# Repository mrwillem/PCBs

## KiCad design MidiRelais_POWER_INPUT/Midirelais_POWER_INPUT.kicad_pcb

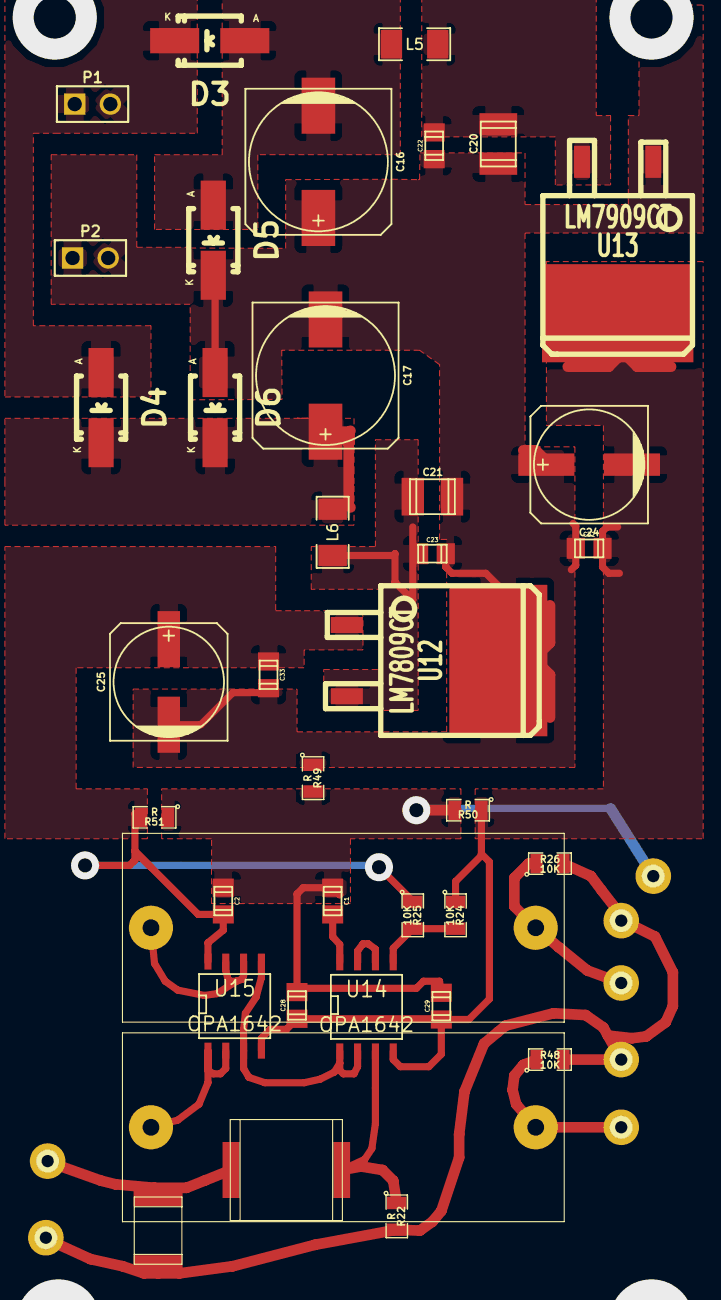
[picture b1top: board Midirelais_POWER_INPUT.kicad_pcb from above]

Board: 2 copper layers, 45 parts (0 on the bottom side), 19 nets.

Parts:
C1, C2, C22, C23, C28, C29, C32, C33: 100nF; c_0805
C16, C17: 470 uF; c_elec_10x10.5
C20, C21: 10uF; c_1210
C24, C25: 47 uF; c_elec_8x6.5
C26: 68pF; Capacitor-Wima-SMD1812-100v-L4,8
C27: 1uF; Capacitor-Wima-SMD2824-63v-L7,2
C30, C31: 10uF; Capacitor-Wima-MKS4-100v-R27K5B13
D3, D4, D5, D6: DIODE; Diode-SMA_Handsoldering_RevA_27July2010
L5, L6: 15 uH 0.08 R; SM1206
P1, P2: CONN_2; PIN_ARRAY_2X1
P3, P12, P13, P14, P15, P16, P17: CONN_1; connect-PAD-01
R22, R49, R50, R51: R; SM0805
R24, R25, R26, R48: 10K; SM0805
U12: LM7809CT; TO263-2
U13: LM7909CT; TO263-2
U14, U15: OPA1642; SO8N

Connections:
AGND: C1.2, C2.2, C28.1, C29.1, P3.1, R49.2, R50.2, R51.1
GND: C26.2, P13.1, P14.1, P15.1, R22.2, R26.2, R48.2
unnamed: C30.2, P16.1, R26.1
unnamed: C31.2, P17.1, R48.1
unnamed: U14.6, U14.7
unnamed: C24.2, C28.2, C29.2, C32.1, R24.1, R50.1, U13.2, U14.4, U15.4
unnamed: C17.1, D4.2, D6.2, L6.1
unnamed: D3.2, D4.1, P1.1, P1.2
unnamed: C16.2, D3.1, D5.1, L5.1
unnamed: C26.1, C27.1, P12.1
unnamed: C27.2, R22.1, U14.3
unnamed: C1.1, C2.1, C25.1, C33.2, R25.1, R51.2, U12.1, U14.8, U15.8
unnamed: R24.2, R25.2, U14.5
unnamed: C20.1, C22.1, L5.2, U13.3
unnamed: C21.2, C23.2, L6.2, U12.3
unnamed: C31.1, U15.1, U15.2
unnamed: C16.1, C17.2, C20.2, C21.1, C22.2, C23.1, C24.1, C25.2, C32.2, C33.1, D5.2, D6.1, P2.1, P2.2, R49.1, U12.2, U13.1
unnamed: U14.1, U14.2, U15.3, U15.5
unnamed: C30.1, U15.6, U15.7

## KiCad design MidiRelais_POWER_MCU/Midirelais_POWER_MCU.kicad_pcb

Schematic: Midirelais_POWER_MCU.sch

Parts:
C1, C18: 1000 uF
C2, C6, C7, C9, C10, C11, C12, C13, C14, C15: 100nF
C3, C4: 22pF
C5: 10nF
C8: 220 uF
CSUP1, CSUP2: 470nF
Cboot1: 100nF
Ccomp1: 1,2 nF
Ccomp2: 22pF
Cfilter1, Cfilter21: 2.2uF
Cin1: 10uF
Cout1: 47uF
Cout_spare1: 47uF
Css1: 8.2nF
D1: 1n914
D2: B340LA-13-F
D7, D8, D9, D10: DIODE
F1: FUSE
K3, K4: CONN_3
L1, L3, L4: 15 uH 0.08 R
L2: 100nH
P1, P2, P7, P8, P12: CONN_2
P3: ISP
P4, P5, P9, P10, P11, P13: CONN_10
P6: CONN_10X2
P14, P15: CONN_6
Q1, Q2, Q3: MOSFET_N
R1, R2, R3, R4, R5, R6, R7, R8, R9, R10, R11, R12, R13, R14, R17, R19, R23, R32, R41, R42, R51, R53, R55, R56, R57: 10K
R15, R21: 100K
R16: 1K
R18, R27, R28, R29, R30, R58, R59: 220R
R20: 270R
R22, R24, R25, R26: 680R
R31: 47R
R33, R34, R35, R36, R37, R38, R39, R40, R43, R44, R45, R46, R47, R48, R49, R50, R52, R54: 100
R60, R61, R62, R63, R64, R65, R66, R67, R68: 0R0
RFBB1: 1.96K
RFBT1: 10.2K
Rcomp1: 48,7K
RenB1: 35,7K
RenT1: 169K
U1: TPS54321DR; MODULE
U2: CRYSTAL_SMD_CERAMIC; MODULE
U3: 93C86; MODULE
U4: TLC592X; MODULE
U5, U8: TPIC6B595; MODULE
U9: PC900; MODULE
U10: ATMEGA8-AI; TQFP32
U11: 74LS14

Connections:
ACA: CSUP1.2, L3.1, P1.1, P1.2 (PM), P12.1, P12.2 (PM)
ACB: CSUP1.1, L4.1, P2.1, P2.2 (PM), P8.1, P8.2 (PM)
ACFA: CSUP2.2, D8.2 (K), D9.1 (A), L3.2
ACFB: CSUP2.1, D7.2 (K), D10.1 (A), L4.2
BOOT: Cboot1.1, U1.1 (BOOT)
CLR: R32.2, R62.1, U5.9 (G), U10.11 ((AIN1)PD7)
CLR1: R62.2, U8.9 (G)
COMP: Ccomp2.1, Rcomp1.1, U1.6 (COMP)
DGND: C1.2, C2.1, C3.1, C4.1, C5.2, C6.2, C7.1, C8.2, C9.2, C10.1, C11.1, C12.1, C13.1, C14.2, C15.1, C18.2, Ccomp1.2, Ccomp2.2, Cfilter1.2, Cfilter21.2, Cin1.2, Cout1.2, Cout_spare1.2, Css1.2, D2.1 (A), D7.1 (A), D8.1 (A), K3.2 (PM), K4.2 (PM), P3.6, P10.9, P13.9, P14.5, P15.5, Q1.S, Q2.S, Q3.S, R15.2, R16.1, R21.2, R41.1, R42.1, R51.2, R53.2, R55.2, R59.1, RFBB1.2, RenB1.2, U1.7 (GND), U1.9 (GND), U2.2, U2.4, U3.7 (ORG), U3.8 (VSS), U4.1 (GND), U4.21 (OE), U5.1 (NC), U5.10 (GND), U5.11 (GND), U5.19 (GND), U5.20 (NC), U8.1 (NC), U8.10 (GND), U8.11 (GND), U8.19 (GND), U8.20 (NC), U9.5 (GND), U10.3 (GND), U10.5 (GND), U10.21 (AGND), U11.7 (GND)
DISPLAY: U4.4 (LE), U10.2 ((XCK/T0)PD4)
EN: RenB1.1, RenT1.2, U1.3 (EN)
MEMCS: U3.1 (CS), U10.14 ((~SS~/OC1B)PB2)
MISO: P3.1, U3.4 (MISO), U10.16 ((MISO)PB4)
MOSI: P3.4, R60.2, R61.2, U8.3 (SDI)
MOSI1: R60.1, U3.3 (MOSI), U10.15 ((MOSI/OC2)PB3)
MOSI2: R61.1, U4.2 (SDI)
MUTE: Q3.G, R55.1, R67.1
MidiMCUBridge: U10.30 ((RXD)PD0), U11.4
unnamed: P14.1, R25.2
unnamed: P14.2, R26.2
unnamed: P11.2, R52.2
unnamed: R30.1, U11.12
unnamed: R28.1, U11.10
unnamed: P11.9, R44.2
unnamed: P11.7, R48.2
unnamed: Q1.D, R50.1
unnamed: P11.5, R49.2
unnamed: P11.3, R50.2
unnamed: P15.2, R24.2
unnamed: P15.1, R22.2
unnamed: K4.3, R30.2
unnamed: K4.1, R29.2
unnamed: K3.3, R28.2
unnamed: K3.1, R27.2
unnamed: P7.2 (PM), R18.1
unnamed: P3.5, R63.2
unnamed: P9.8, R35.2
unnamed: P9.3, R40.2
unnamed: P9.4, R39.2
unnamed: P9.5, R38.2
unnamed: P9.6, R37.2
unnamed: P9.7, R36.2
unnamed: P9.9, R34.2
unnamed: P11.8, R45.2
unnamed: P11.4, R47.2
unnamed: P11.6, R46.2
unnamed: P11.10, R43.2
unnamed: P9.10, R33.2
unnamed: P4.2, R13.1, R41.2
unnamed: P5.7, R7.2, R9.1
unnamed: P5.5, R11.2, R14.1
unnamed: P5.4, R14.2, R17.1
unnamed: P5.3, R17.2, R19.2
unnamed: P5.2, R19.1, R42.2
unnamed: R25.1, R33.1, U8.7 (D3)
unnamed: R26.1, R34.1, U8.6 (D2)
unnamed: C3.2, U2.3, U10.7 (PB6(XTAL1/TOSC1))
unnamed: R65.2, U10.25 ((ADC2)PC2)
unnamed: C9.1, R64.2, U3.5 (VCC)
unnamed: R68.2, U10.28 ((ADC5/SCL)PC5)
unnamed: R67.2, U10.27 ((ADC4/SDA)PC4)
unnamed: R66.2, U10.26 ((ADC3)PC3)
unnamed: R24.1, R36.1, U8.15 (D5)
unnamed: R22.1, R35.1, U8.14 (D4)
unnamed: R56.2, U8.8 (CLR)
unnamed: P6.13, U4.6 (OUT1)
unnamed: R16.2, U4.23 (REXT)
unnamed: P6.15, U4.5 (OUT0)
unnamed: P6.11, U4.7 (OUT2)
unnamed: P6.9, U4.8 (OUT3)
unnamed: P6.7, U4.9 (OUT4)
unnamed: P6.5, U4.10 (OUT5)
unnamed: P6.4, U4.14 (OUT9)
unnamed: P6.2, U4.13 (OUT8)
unnamed: Q2.D, R54.1
unnamed: P9.2, R54.2
unnamed: P6.3, U4.11 (OUT6)
unnamed: P6.1, U4.12 (OUT7)
unnamed: P6.16, U4.20 (OUT16)
unnamed: P6.14, U4.19 (OUT15)
unnamed: P6.12, U4.18 (OUT14)
unnamed: P6.10, U4.17 (OUT13)
unnamed: P6.8, U4.16 (OUT12)
unnamed: P6.6, U4.15 (OUT11)
unnamed: R57.2, U5.8 (CLR)
unnamed: U5.3 (SDI), U8.18 (SDO)
unnamed: R20.1, U9.4 (VOUT), U11.1
unnamed: D1.2 (K), R18.2, U9.1 (Anode)
unnamed: D1.1 (A), P7.1, U9.2 (Kathode)
unnamed: P10.8, P13.8, Q3.D, R52.1
unnamed: P10.7, P13.7, R47.1, U5.16 (D6)
unnamed: P10.6, P13.6, R49.1, U5.15 (D5)
unnamed: P10.5, P13.5, R46.1, U5.14 (D4)
unnamed: P10.4, P13.4, R48.1, U5.4 (D0)
unnamed: P10.3, P13.3, R45.1, U5.5 (D1)
unnamed: P10.2, P13.2, R44.1, U5.6 (D2)
unnamed: P10.1, P13.1, R43.1, U5.7 (D3)
unnamed: Ccomp1.1, Rcomp1.2
unnamed: P5.8, R4.2, R7.1
unnamed: Css1.1, U1.4 (SS)
unnamed: P4.8, R3.2, R5.1
unnamed: R23.1, R63.1, U10.29 (PC6(~RESET~))
unnamed: C5.1, R31.2, U10.18 (AVCC)
unnamed: C6.1, U10.20 (AREF)
unnamed: P4.5, R8.2, R10.1
unnamed: P4.4, R10.2, R12.1
unnamed: P4.6, R6.2, R8.1
unnamed: P4.7, R5.2, R6.1
unnamed: P4.9, R1.2, R3.1
unnamed: P4.3, R12.2, R13.2
unnamed: C4.2, U2.1, U10.8 (PB7(XTAL2/TOSC2))
unnamed: P5.6, R9.2, R11.1
unnamed: U11.2, U11.3, U11.11, U11.13
unnamed: P14.3, R37.1, U8.5 (D1)
unnamed: P14.4, R38.1, U8.4 (D0)
unnamed: P15.4, R40.1, U8.17 (D7)
unnamed: P15.3, R39.1, U8.16 (D6)
unnamed: P5.9, R2.2, R4.1
PH: Cboot1.2, D2.2 (K), L1.1, U1.8 (PH)
POWERAMP2: Q1.G, R51.1, R68.1
RCLK: U5.12 (SCLK), U8.12 (SCLK), U10.10 ((AIN0)PD6)
SCK: P3.3, R58.1, R59.2, U3.2 (CLK), U4.3 (CLK), U5.13 (SS), U8.13 (SS), U10.17 ((SCK)PB5)
SENSE: RFBB1.1, RFBT1.2, U1.5 (VSENSE)
SETUP: Q2.G, R53.1, U10.1 ((INT1)PD3)
SWITCH1: P5.1, R21.1, R66.1
SWITCH2: P4.1, R15.1, R65.1
V+: C15.2, C18.1, Cin1.1, F1.1, RenT1.1, U1.2 (VIN)
VCC: C2.2, C7.2, C8.1, C10.2, C11.2, C12.2, C13.2, C14.1, Cfilter1.1, Cfilter21.1, L2.2, P3.2, P4.10, P5.10, P6.17, P6.18, P6.19, P6.20, P9.1, P10.10, P11.1, P13.10, P14.6, P15.6, R1.1, R2.1, R20.2, R23.2, R27.1, R29.1, R31.1, R32.1, R56.1, R57.1, R58.2, R64.1, U4.24 (VDD), U5.2 (VCC), U8.2 (VCC), U9.6 (VCC), U10.4 (VCC), U10.6 (VCC), U11.14 (VCC)
VFUSE: C1.1, D9.2 (K), D10.2 (K), F1.2
VPRE5: Cout1.1, Cout_spare1.1, L1.2, L2.1, RFBT1.1

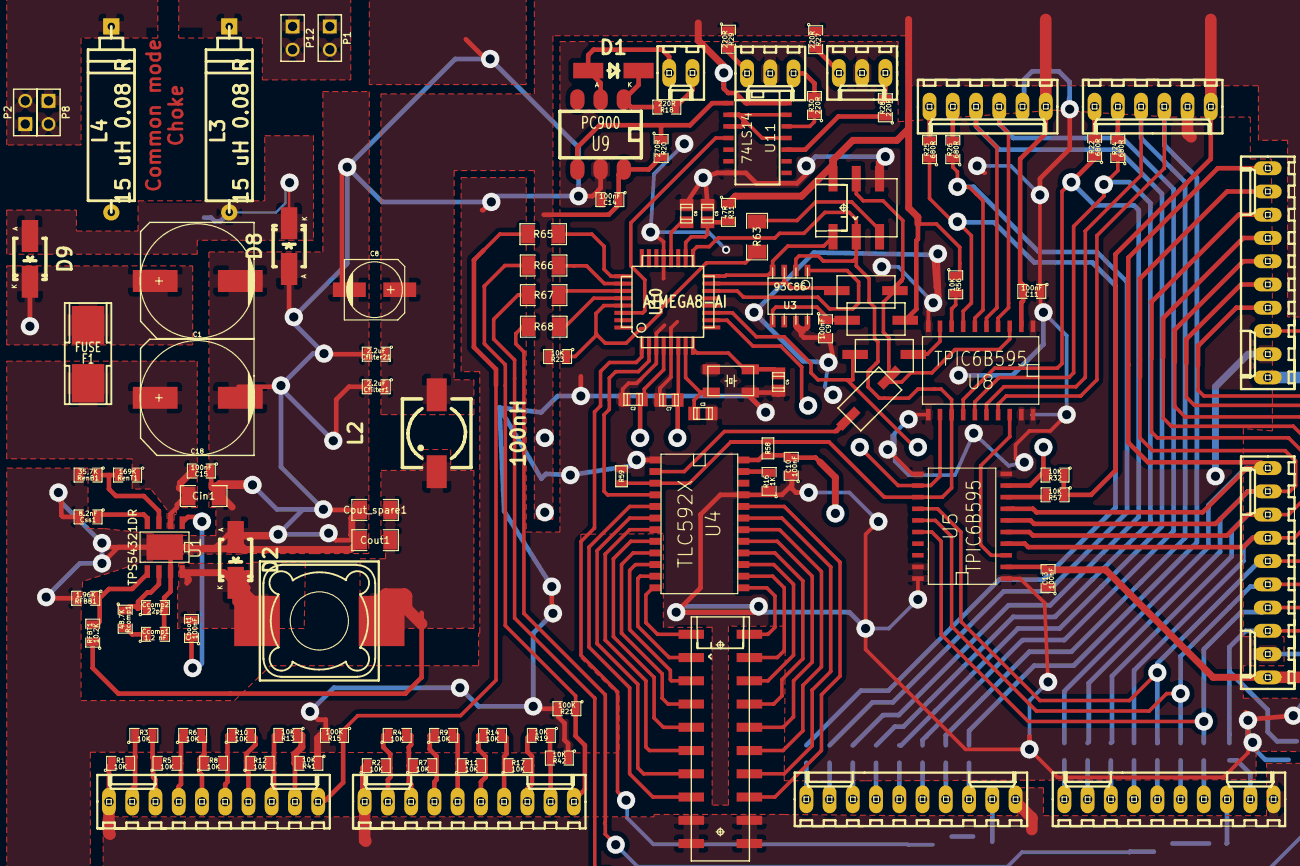
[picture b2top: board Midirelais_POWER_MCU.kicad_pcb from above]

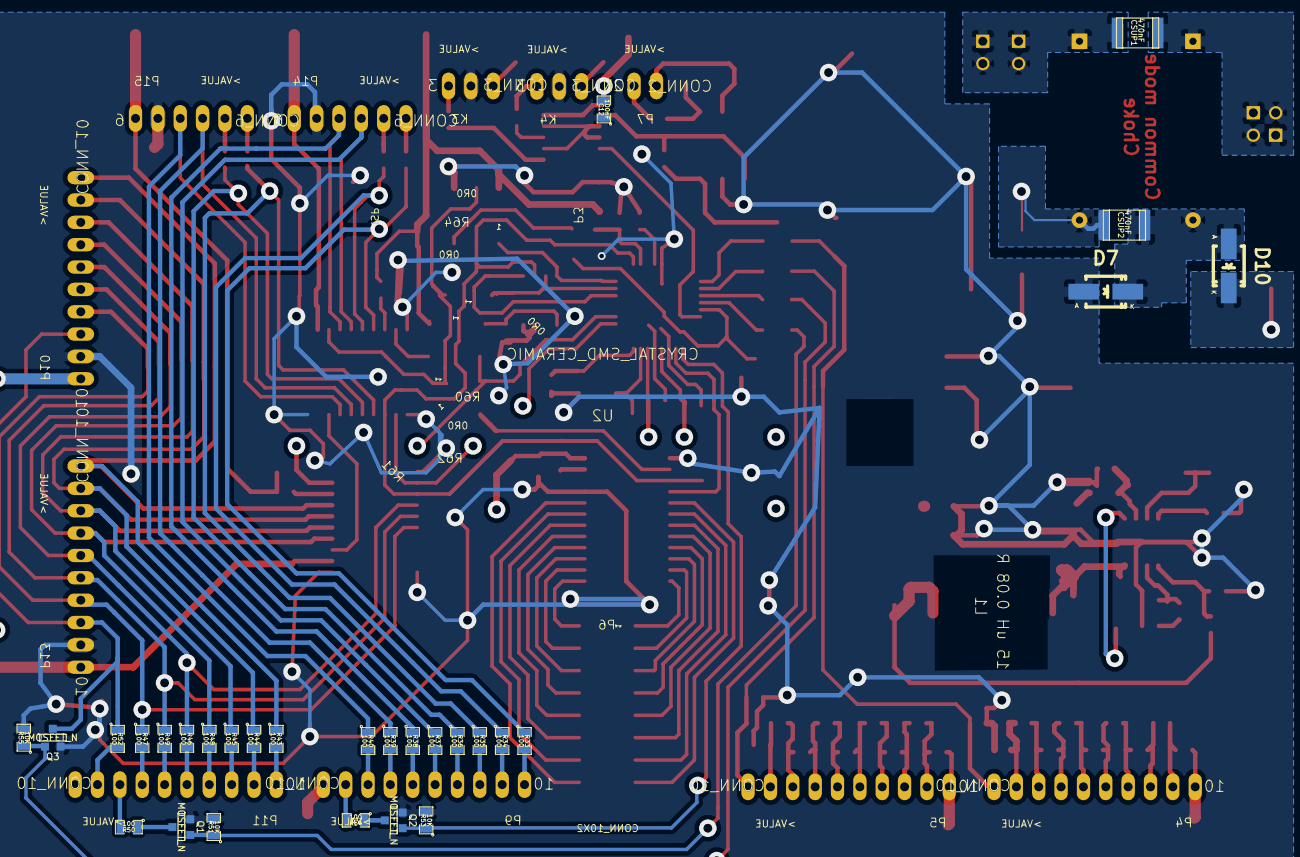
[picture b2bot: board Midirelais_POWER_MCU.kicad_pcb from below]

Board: 4 copper layers, 140 parts (29 on the bottom side), 130 nets.

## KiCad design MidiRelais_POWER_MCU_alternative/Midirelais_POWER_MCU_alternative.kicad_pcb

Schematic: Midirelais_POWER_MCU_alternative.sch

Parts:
C1, C8, C15, C36: 10uF; C_1206
C2: CP; c_elec_4x5.7
C3, C4: 22pF; C_0805
C5, C9, C10, C11, C12, C13, C14, C21, C22, C25, C26, C27, C28, C30, C31, C32, C33, C34, C35: 100nF; C_0805
C6, C7: 10uF; C_0805
C16, C17, C23, C24: 4.7uF; C_1206
C18, C20: 2.2uF; C_0805
C19: 4,7uF; C_1206
C29: 2,2uF; C_0805
C37: 10nF; C_0805
D1: 1n914; SOD-323-Handsoldering
JP1: Jumper_NC_Small; NetTie-I_Connected_SMD
K3, K4: CONN_3; PINHEAD1-3
P1: CONN_01X04; PINHEAD1-4
P2: CONN_02X05; Pin_Header_Straight_2x05_Pitch1.27mm
P3, P4, P9, P10, P11, P13: CONN_10; PINHEAD1-10
P6: CONN_10X2; Pin_Header_Straight_2x10
P7: CONN_2; PINHEAD1-2
P14, P15: CONN_6; PINHEAD1-6
Q1, Q2, Q3: Q_NMOS_GSD; SOT-23_Handsoldering
R1, R2, R23, R32, R51, R53, R55, R56, R69, R73: 10K; R_0805_HandSoldering
R3, R4: 100K; R_0805_HandSoldering
R5, R6, R7, R8, R9, R10, R11, R12: 0R0; R_0805_HandSoldering
R16: 2K; R_0805_HandSoldering
R18, R27, R28, R29, R30: 220R; R_0805_HandSoldering
R20: 270R; R_0805_HandSoldering
R22, R24, R25, R26, R52, R54: 100; R_0805_HandSoldering
R57: 10K; R_1206
RP1, RP2, RP3, RP4, RP5, RP6, RP7, RP8: R_PACK4; R_Array_Convex_4x1206
U1: 25LC1024; SOIC-8_3.9x4.9mm_Pitch1.27mm
U2: CRYSTAL_SMD_CERAMIC; Xtal_Ceramic_5x3.2
U3: LDF333DT-TR; TO-252-2Lead
U4: TLC592X; SOIC-24_7.5x15.4mm_Pitch1.27mm
U5, U8: TPIC6B595; SOIC-20_7.5x12.8mm_Pitch1.27mm
U6: STM32F103CB; LQFP-48_7x7mm_Pitch0.5mm
U7: txb0102; VSSOP-8_2.4x2.1mm_Pitch0.5mm
U9: PC900; SO6_DIL_GULLWING
U11: 74LS14; SOIC-14_3.9x8.7mm_Pitch1.27mm

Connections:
/OUT0: P6.16, U4.5 (OUT0)
/OUT1: P6.15, U4.6 (OUT1)
/OUT2: P6.14, U4.7 (OUT2)
/OUT3: P6.13, U4.8 (OUT3)
/OUT4: P6.12, U4.9 (OUT4)
/OUT5: P6.11, U4.10 (OUT5)
/OUT6: P6.10, U4.11 (OUT6)
/OUT7: P6.9, U4.12 (OUT7)
/OUT8: P6.8, U4.13 (OUT8)
/OUT9: P6.7, U4.14 (OUT9)
/OUT10: P6.6, U4.15 (OUT11)
/OUT11: P6.5, U4.16 (OUT12)
/OUT12: P6.4, U4.17 (OUT13)
/OUT13: P6.3, U4.18 (OUT14)
/OUT14: P6.2, U4.19 (OUT15)
/OUT15: P6.1, U4.20 (OUT16)
CLR: R7.1, U5.9 (G), U8.9 (G)
DGND: C1.2, C2.2, C5.1, C6.1, C7.1, C8.2, C9.2, C10.1, C11.1, C12.1, C13.1, C14.2, C15.2, C16.2, C17.2, C18.2, C19.2, C20.2, C21.1, C22.1, C23.1, C24.1, C25.1, C26.2, C27.1, C28.1, C29.1, C30.2, C31.2, C32.1, C33.2, C34.1, C35.2, C36.2, C37.2, JP1.2, K3.2 (PM), K4.2 (PM), P1.1, P1.2, P2.3, P2.5, P2.7, P2.9, P10.2, P13.2, P14.2, P15.2, Q1.2 (S), Q2.2 (S), Q3.2 (S), R1.1, R2.1, R3.1, R4.1, R23.2, R51.1, R53.2, R55.2, U1.4 (VSS), U3.2 (GND), U4.1 (GND), U4.21 (OE), U5.1 (NC), U5.10 (GND), U5.11 (GND), U5.19 (GND), U5.20 (NC), U6.8 (VSSA), U6.20 (PB2/BOOT1), U6.23 (VSS), U6.35 (VSS), U6.44 (BOOT0), U6.47 (VSS), U7.2 (GND), U8.1 (NC), U8.10 (GND), U8.11 (GND), U8.19 (GND), U8.20 (NC), U9.5 (GND), U11.3, U11.7 (GND), U11.13; also elsewhere on the board
DISPLAY: R73.1, U4.4 (LE), U6.19 (PB1/ADC12_IN9/TIM3_CH4)
MCUMIDIRX: U6.13 (USART2_RX/ADC12_IN3/TIM2_CH4/PA3), U7.4 (A2)
MCUMIDITX: U6.12 (USART2_TX/ADC12_IN2/TIM2_CH3/PA2), U7.5 (A1)
MEMCS: R69.2, U1.1 (CS), U6.25 (PB12/SPI2_NSS/I2C2_SMBA/USART3_CK/TIM1_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)
MIDIEN: R23.1, U6.11 (USART2_RTS/ADC12_IN1/TIM2_CH2/PA1), U7.6 (OE)
MIDIRX: R20.1, U7.1 (B2), U9.4 (VOUT), U11.5
MIDITX: U7.8 (B1), U11.9
MISO: U1.2 (MISO), U6.27 (PB14/SPI2_MISO/USART3_RTS/TIM1_CH2N)
MOSI: U1.5 (MOSI), U4.2 (SDI), U6.28 (PB15/SPI2_MOSI/TIM1_CH3N), U8.3 (SDI)
MUTE: Q1.1 (G), R9.1, R55.1
unnamed: C3.2, U2.3 (OSC), U6.6 (PD1/OSC_OUT)
unnamed: C4.2, U2.1 (OSC), U6.5 (PD0/OSC_IN)
unnamed: C18.1, C31.1, R5.2, U7.7 (VCCB)
unnamed: C21.2, C23.2, P4.10, RP5.1
unnamed: C22.2, C24.2, P3.10, RP7.1
unnamed: D1.1 (A), P7.1, U9.2 (Kathode)
unnamed: D1.2 (K), R18.2, U9.1 (Anode)
unnamed: K3.1, R27.2
unnamed: K3.3, R28.2
unnamed: K4.1, R29.2
unnamed: K4.3, R30.2
unnamed: P3.2, R2.2, RP8.5 (R4)
unnamed: P3.3, RP8.4, RP8.6 (R3)
unnamed: P3.4, RP8.3, RP8.7 (R2)
unnamed: P3.5, RP8.2, RP8.8 (R1)
unnamed: P3.6, RP7.5 (R4), RP8.1
unnamed: P3.7, RP7.4, RP7.6 (R3)
unnamed: P3.8, RP7.3, RP7.7 (R2)
unnamed: P3.9, RP7.2, RP7.8 (R1)
unnamed: P4.2, R1.2, RP6.5 (R4)
unnamed: P4.3, RP6.4, RP6.6 (R3)
unnamed: P4.4, RP6.3, RP6.7 (R2)
unnamed: P4.5, RP6.2, RP6.8 (R1)
unnamed: P4.6, RP5.5 (R4), RP6.1
unnamed: P4.7, RP5.4, RP5.6 (R3)
unnamed: P4.8, RP5.3, RP5.7 (R2)
unnamed: P4.9, RP5.2, RP5.8 (R1)
unnamed: P7.2 (PM), R18.1
unnamed: P9.2, R54.2
unnamed: P9.3, RP4.5 (R4)
unnamed: P9.4, RP4.6 (R3)
unnamed: P9.5, RP4.7 (R2)
unnamed: P9.6, RP4.8 (R1)
unnamed: P9.7, RP3.5 (R4)
unnamed: P9.8, RP3.6 (R3)
unnamed: P9.9, RP3.7 (R2)
unnamed: P9.10, RP3.8 (R1)
unnamed: P10.3, P13.3, Q1.3 (D), R52.1
unnamed: P10.4, P13.4, RP2.7 (R2), U5.16 (D6)
unnamed: P10.5, P13.5, RP2.6 (R3), U5.15 (D5)
unnamed: P10.6, P13.6, RP2.5 (R4), U5.14 (D4)
unnamed: P10.7, P13.7, RP1.8 (R1), U5.7 (D3)
unnamed: P10.8, P13.8, RP1.7 (R2), U5.6 (D2)
unnamed: P10.9, P13.9, RP1.6 (R3), U5.5 (D1)
unnamed: P10.10, P13.10, RP1.5 (R4), U5.4 (D0)
unnamed: P11.2, R52.2
unnamed: P11.3, RP2.8 (R1)
unnamed: P11.4, RP2.2
unnamed: P11.5, RP2.3
unnamed: P11.6, RP2.4
unnamed: P11.7, RP1.1
unnamed: P11.8, RP1.2
unnamed: P11.9, RP1.3
unnamed: P11.10, RP1.4
unnamed: P14.3, RP4.2, U8.7 (D3)
unnamed: P14.4, RP4.1, U8.6 (D2)
unnamed: P14.5, R26.2
unnamed: P14.6, R25.2
unnamed: P15.3, RP4.4, U8.17 (D7)
unnamed: P15.4, RP4.3, U8.16 (D6)
unnamed: P15.5, R24.2
unnamed: P15.6, R22.2
unnamed: Q2.3 (D), RP2.1
unnamed: Q3.3 (D), R54.1
unnamed: R6.2, U6.32 (USART1_CTS/CANRX/USBDM/TIM1_CH4/PA11)
unnamed: R9.2, U6.30 (USART1_TX/TIM1_CH2/PA9)
unnamed: R10.2, U6.31 (USART1_RX/TIM1_CH3/PA10)
unnamed: R16.2, U4.23 (REXT)
unnamed: R22.1, RP3.3, U8.14 (D4)
unnamed: R24.1, RP3.4, U8.15 (D5)
unnamed: R25.1, RP3.1, U8.4 (D0)
unnamed: R26.1, RP3.2, U8.5 (D1)
unnamed: R28.1, U11.10
unnamed: R30.1, U11.2
unnamed: R7.2, R32.2, U6.33 (USART1_RTS/CANTX/USBDP/TIM1_ETR/PA12)
unnamed: R8.2, R51.2, U6.29 (USART1_CK/TIM1_CH1/MCO/PA8)
unnamed: R56.2, U8.8 (CLR)
unnamed: R57.2, U5.8 (CLR)
unnamed: U5.3 (SDI), U8.18 (SDO)
unnamed: U11.1, U11.6
unnamed: U11.8, U11.11
POWERAMP2: Q2.1 (G), R8.1
RCLK: R6.1, U5.12 (SCLK), U8.12 (SCLK)
RESET: C32.2, P2.10, U6.7 (~NRST)
SCK: U1.6 (SCK), U4.3 (CLK), U5.13 (SS), U6.26 (PB13/SPI2_SCK/USART3_CTS/TIM1_CH1N), U8.13 (SS)
SETUP: Q3.1 (G), R10.1, R53.1
STMVCC: C2.1, C5.2, C6.2, C7.2, C9.1, C25.2, C26.1, C27.2, C28.2, C29.2, C30.1, C34.2, R11.2, R12.2, R69.1, R73.2, U1.3 (WP), U1.7 (HOLD), U1.8 (VCC), U3.3 (VOUT), U6.1 (VBAT), U6.9 (VDDA), U6.24 (VDD), U6.36 (VDD), U6.48 (VDD), U7.3 (VCCA)
SWCLK: P2.4, U6.37 (JTCK/SWCLK/PA14)
SWDIO: P2.2, U6.34 (JTMS/SWDIO/PA13)
SWITCH1: P3.1, R4.2, U6.14 (SPI1_NSS/USART2_CK/ADC12_IN4/PA4)
SWITCH2: P4.1, R3.2, U6.15 (SPI1_SCK/ADC12_IN5/PA5)
SWO: P2.6, U6.39 (PB3/JTDO)
TLCVCC: C12.2, C19.1, R11.1, R16.1, U4.24 (VDD)
U5VCC: C10.2, C33.1, P2.1, R12.1, R32.1, R56.1, R57.1, U5.2 (VCC), U8.2 (VCC); also elsewhere on the board
VCC: C1.1, C8.1, C11.2, C13.2, C14.1, C15.1, C16.1, C17.1, C20.1, C35.1, C36.1, C37.1, P1.3, P1.4, P6.17, P6.18, P6.19, P6.20, P9.1, P10.1, P11.1, P13.1, P14.1, P15.1, R5.1, R20.2, R27.1, R29.1, U3.1 (VIN), U9.6 (VCC), U11.14 (VCC)
xtalgnd: C3.1, C4.1, JP1.1, U2.2 (GND), U2.4 (GND)

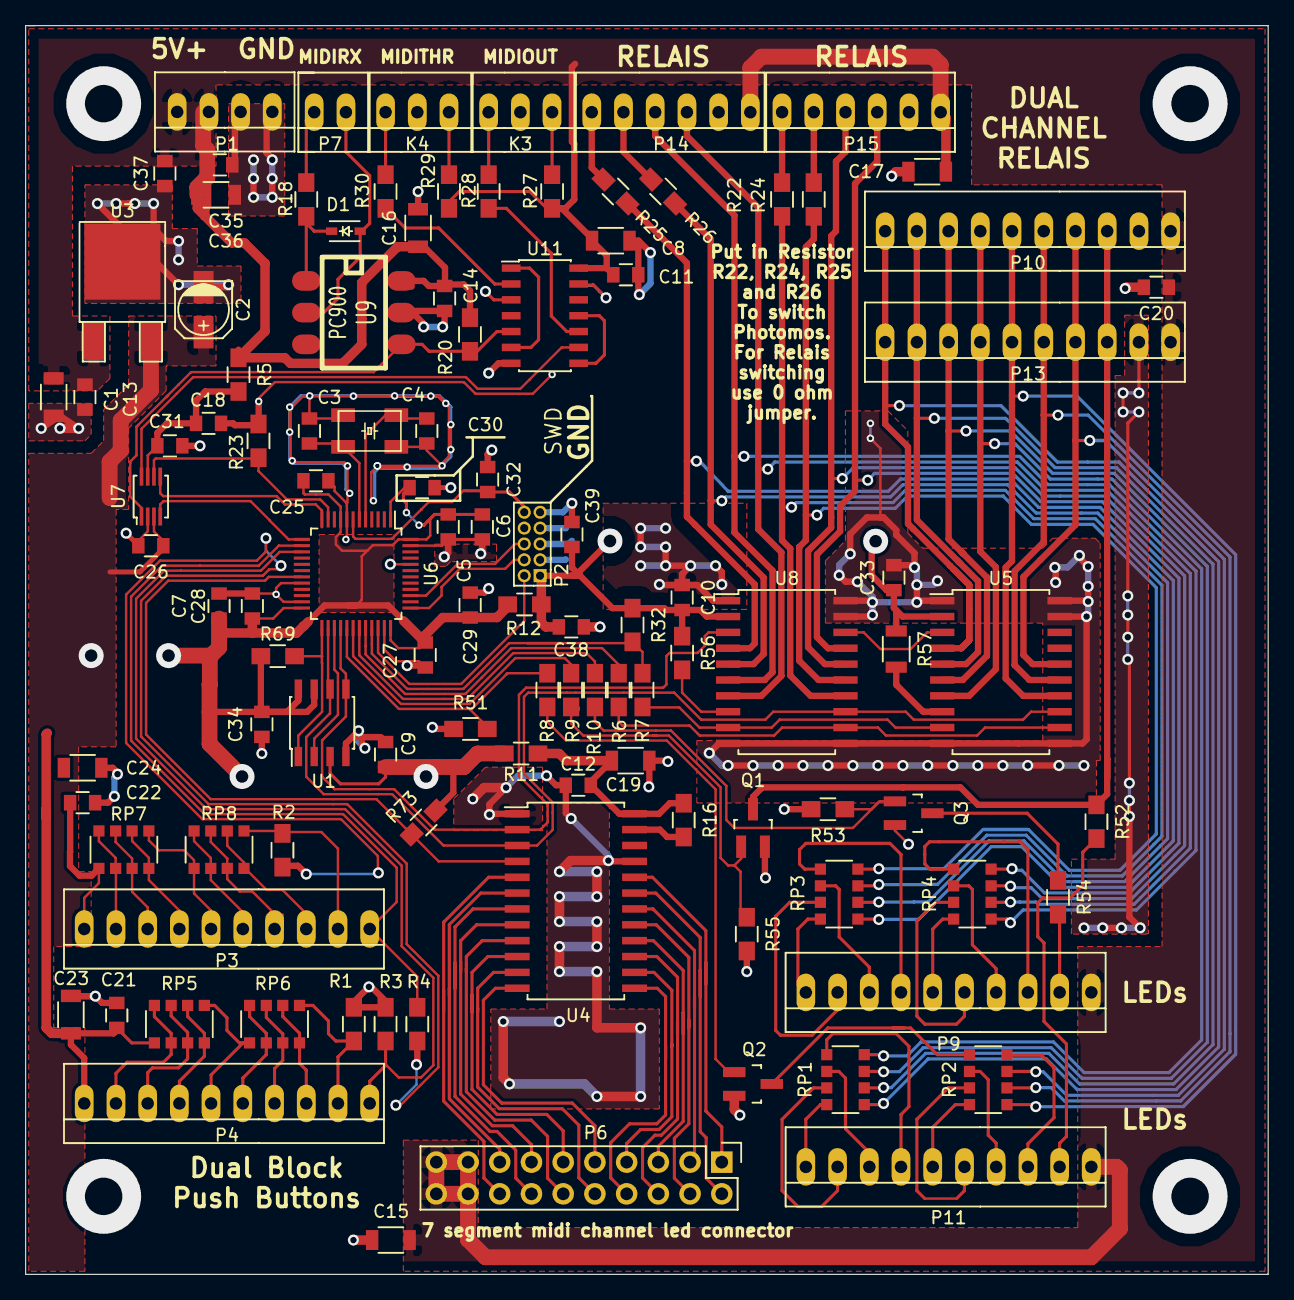
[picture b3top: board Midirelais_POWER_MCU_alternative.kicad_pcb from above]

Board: 4 copper layers, 99.5 x 100.0 mm, 110 parts (0 on the bottom side), 124 nets.

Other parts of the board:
C38: 10uF; C_0805
C39: 100nF; C_0805

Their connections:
DGND: C38.2, C39.2; also elsewhere on the board
U5VCC: C38.1, C39.1; also elsewhere on the board

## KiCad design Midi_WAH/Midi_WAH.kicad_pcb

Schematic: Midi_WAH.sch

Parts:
C1, C3, C15, C16, C35: 100n; C_0805
C4, C44, C45, C46, C47, C48, C49, C52, C53, C54, C55, C61: 10u; c_elec_4x5.8
C7, C8, C9, C10, C11, C12, C13, C14, C17, C18, C19, C20, C21, C22, C30, C31, C32, C33, C34, C37, C38: 100nF; C_0805
C23, C24, C25, C26, C40, C41, C42, C43: 5u; c_elec_4x5.8
C28, C29: 22pF; C_0805
C36: 56pF; C_0805
C39: 10uF; C_0805
C50, C51: 100 nF; C_0805
C56, C57: 10uF; C_0805_HandSoldering
C58: 10nF; C_0805_HandSoldering
C59: 1uF; C_0805_HandSoldering
D1, D2, D3, D4, D5, D6, D7, D8, D9, D10, D11, D12, D13, D14, D15, D16, D17, D18, D19, D20, D21, D22, D23, D24, D25, D26, D27, D28, D29, D30, D31, D32, D33, D34, D35, D36, D37, D38, D39, D40, D41, D42, D43, D44, D45, D46, D47, D48, D49, D50, D51, D52, D53, D54, D55, D56, D57, D58, D59, D60, D61, D62, D63, D64, D65, D66, D67, D68, D69, D70, D71, D72, D73, D74, D75, D76, D77, D78, D79, D80, D81, D82, D83, D84, D85, D86, D87, D88, D89, D90, D91, D92, D93, D94, D95, D96: LED
JP1: Jumper_NC_Small; NetTie-I_Connected_SMD
L1, L2, L3: INDUCTOR; C_0805_HandSoldering
P1, P2: CONN_6
P3: CONN_5X2
P4: I2Cext
P5, P6, P7, P8, P9, P10, P11, P12, P13, P14: CONN_1; hole
R1, R2, R3, R7, R73: 2,5K
R4, R5: 100K
R8, R9, R10: 220R
R11, R12, R13, R14, R15, R16, R17, R18, R19, R20, R21, R22, R23, R24, R25, R26, R27, R28, R29, R30, R31, R32, R33, R38, R39, R40, R41, R42, R43, R44, R45, R46, R47, R48, R49, R50, R51, R67: 10K
R35, R36, R52, R53, R54, R55, R56, R57, R58, R59, R60, R61, R62, R63, R64, R65, R66: 0R0
R68: ???
S1, S2, S3, S4, S6, S7, S8: ENCODER
S5, S9, S10, S11, S12, S13, S14, S15, S16: DTS-6; switch-tact-DTS-6
U1, U3, U4, U5: TLC5947DAP; MODULE
U8: STM32F103RB; LQFP64
U9, U10, U11: 7SEGMENTLED-COMMONCATODE_HDSM533_SMD_16SEP2013
U12: TLC592X; SOIC-24_7.5x15.4mm_Pitch1.27mm
U13: CRYSTAL_SMD_CERAMIC; MODULE

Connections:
+3.3V: C1.2, C3.2, C15.2, C16.2, C30.2, C31.2, C32.2, C33.2, C34.2, C35.1, C38.1, C39.2, C44.1, C45.1, C46.1, C47.1, C48.1, C49.1, C50.1, C51.1, C52.1, C53.1, C54.1, C55.1, C56.2, C57.2, C58.2, C59.2, C61.1, L1.1, P2.1, P2.2, P3.1, R7.1, R8.1, R11.2, R12.2, R13.2, R14.2, R15.2, R16.2, R17.2, R18.2, R21.2, R22.2, R23.2, R24.2, R25.2, R26.2, R30.1, R33.1, R67.2, S12.1, S12.2, S16.1, S16.2, U1.32 (VCC), U3.32 (VCC), U4.32 (VCC), U5.32 (VCC), U8.1 (VBAT), U8.13 (VDDA), U8.19 (VDD), U8.32 (VDD), U8.48 (VDD), U8.64 (VDD), U12.24 (VDD)
+5V: C4.1, C23.1, C24.1, C25.1, C26.1, C40.1, C41.1, C42.1, C43.1, D1.1 (A), D2.1 (A), D3.1 (A), D4.1 (A), D5.1 (A), D6.1 (A), D7.1 (A), D8.1 (A), D9.1 (A), D10.1 (A), D11.1 (A), D12.1 (A), D13.1 (A), D14.1 (A), D15.1 (A), D16.1 (A), D17.1 (A), D18.1 (A), D19.1 (A), D20.1 (A), D21.1 (A), D22.1 (A), D23.1 (A), D24.1 (A), D25.1 (A), D26.1 (A), D27.1 (A), D28.1 (A), D29.1 (A), D30.1 (A), D31.1 (A), D32.1 (A), D33.1 (A), D34.1 (A), D35.1 (A), D36.1 (A), D37.1 (A), D38.1 (A), D39.1 (A), D40.1 (A), D41.1 (A), D42.1 (A), D43.1 (A), D44.1 (A), D45.1 (A), D46.1 (A), D47.1 (A), D48.1 (A), D49.1 (A), D50.1 (A), D51.1 (A), D52.1 (A), D53.1 (A), D54.1 (A), D55.1 (A), D56.1 (A), D57.1 (A), D58.1 (A), D59.1 (A), D60.1 (A), D61.1 (A), D62.1 (A), D63.1 (A), D64.1 (A), D65.1 (A), D66.1 (A), D67.1 (A), D68.1 (A), D69.1 (A), D70.1 (A), D71.1 (A), D72.1 (A), D73.1 (A), D74.1 (A), D75.1 (A), D76.1 (A), D77.1 (A), D78.1 (A), D79.1 (A), D80.1 (A), D81.1 (A), D82.1 (A), D83.1 (A), D84.1 (A), D85.1 (A), D86.1 (A), D87.1 (A), D88.1 (A), D89.1 (A), D90.1 (A), D91.1 (A), D92.1 (A), D93.1 (A), D94.1 (A), D95.1 (A), D96.1 (A), L2.1, L3.1, P2.5, P2.6
/LED0: D1.2 (K), U12.9 (OUT4)
/LED1: D2.2 (K), U12.10 (OUT5)
/LED2: D3.2 (K), U12.11 (OUT6)
/LED3: D4.2 (K), U12.12 (OUT7)
/LED4: D5.2 (K), U12.8 (OUT3)
/LED5: D6.2 (K), U12.7 (OUT2)
/LED6: D7.2 (K), U12.13 (OUT8)
/LED7: D8.2 (K), U12.14 (OUT9)
/LED8: D9.2 (K), U12.15 (OUT11)
/LED9: D10.2 (K), U12.16 (OUT12)
/LED10: D11.2 (K), U12.17 (OUT13)
/LED11: D12.2 (K), U12.18 (OUT14)
/LED12: D49.2 (K), U1.21 (OUT16)
/LED13: D50.2 (K), U1.22 (OUT17)
/LED14: D51.2 (K), U1.28 (OUT23)
/LED15: D52.2 (K), U1.27 (OUT22)
/LED16: D53.2 (K), U1.26 (OUT21)
/LED17: D54.2 (K), U1.25 (OUT20)
/LED18: D55.2 (K), U1.24 (OUT19)
/LED19: D56.2 (K), U1.23 (OUT18)
/LED20: D57.2 (K), U1.18 (OUT13)
/LED21: D58.2 (K), U1.17 (OUT12)
/LED22: D59.2 (K), U1.19 (OUT14)
/LED23: D60.2 (K), U1.20 (OUT15)
/LED24: D13.2 (K), U1.13 (OUT8)
/LED25: D14.2 (K), U1.14 (OUT9)
/LED26: D15.2 (K), U1.16 (OUT11)
/LED27: D16.2 (K), U1.15 (OUT10)
/LED28: D17.2 (K), U1.10 (OUT5)
/LED29: D18.2 (K), U1.9 (OUT4)
/LED30: D19.2 (K), U1.8 (OUT3)
/LED31: D20.2 (K), U1.7 (OUT2)
/LED32: D21.2 (K), U1.6 (OUT1)
/LED33: D22.2 (K), U1.5 (OUT0)
/LED34: D23.2 (K), U1.11 (OUT6)
/LED35: D24.2 (K), U1.12 (OUT7)
/LED36: D61.2 (K), U3.21 (OUT16)
/LED37: D62.2 (K), U3.22 (OUT17)
/LED38: D63.2 (K), U3.28 (OUT23)
/LED39: D64.2 (K), U3.27 (OUT22)
/LED40: D65.2 (K), U3.26 (OUT21)
/LED41: D66.2 (K), U3.25 (OUT20)
/LED42: D67.2 (K), U3.24 (OUT19)
/LED43: D68.2 (K), U3.23 (OUT18)
/LED44: D69.2 (K), U3.18 (OUT13)
/LED45: D70.2 (K), U3.17 (OUT12)
/LED46: D71.2 (K), U3.19 (OUT14)
/LED47: D72.2 (K), U3.20 (OUT15)
/LED48: D25.2 (K), U3.13 (OUT8)
/LED49: D26.2 (K), U3.14 (OUT9)
/LED50: D27.2 (K), U3.16 (OUT11)
/LED51: D28.2 (K), U3.15 (OUT10)
/LED52: D29.2 (K), U3.10 (OUT5)
/LED53: D30.2 (K), U3.9 (OUT4)
/LED54: D31.2 (K), U3.8 (OUT3)
/LED55: D32.2 (K), U3.7 (OUT2)
/LED56: D33.2 (K), U3.6 (OUT1)
/LED57: D34.2 (K), U3.5 (OUT0)
/LED58: D35.2 (K), U3.11 (OUT6)
/LED59: D36.2 (K), U3.12 (OUT7)
/LED60: D73.2 (K), U4.21 (OUT16)
/LED61: D74.2 (K), U4.22 (OUT17)
/LED62: D75.2 (K), U4.28 (OUT23)
/LED63: D76.2 (K), U4.27 (OUT22)
/LED64: D77.2 (K), U4.26 (OUT21)
/LED65: D78.2 (K), U4.25 (OUT20)
/LED66: D79.2 (K), U4.24 (OUT19)
/LED67: D80.2 (K), U4.23 (OUT18)
/LED68: D81.2 (K), U4.18 (OUT13)
/LED69: D82.2 (K), U4.17 (OUT12)
/LED70: D83.2 (K), U4.19 (OUT14)
/LED71: D84.2 (K), U4.20 (OUT15)
/LED72: D37.2 (K), U4.13 (OUT8)
/LED73: D38.2 (K), U4.14 (OUT9)
/LED74: D39.2 (K), U4.16 (OUT11)
/LED75: D40.2 (K), U4.15 (OUT10)
/LED76: D41.2 (K), U4.10 (OUT5)
/LED77: D42.2 (K), U4.9 (OUT4)
/LED78: D43.2 (K), U4.8 (OUT3)
/LED79: D44.2 (K), U4.7 (OUT2)
/LED80: D45.2 (K), U4.6 (OUT1)
/LED81: D46.2 (K), U4.5 (OUT0)
/LED82: D47.2 (K), U4.11 (OUT6)
/LED83: D48.2 (K), U4.12 (OUT7)
/LED84: D85.2 (K), U5.13 (OUT8)
/LED85: D86.2 (K), U5.14 (OUT9)
/LED86: D87.2 (K), U5.16 (OUT11)
/LED87: D88.2 (K), U5.15 (OUT10)
/LED88: D89.2 (K), U5.10 (OUT5)
/LED89: D90.2 (K), U5.9 (OUT4)
/LED90: D91.2 (K), U5.8 (OUT3)
/LED91: D92.2 (K), U5.7 (OUT2)
/LED92: D93.2 (K), U5.6 (OUT1)
/LED93: D94.2 (K), U5.5 (OUT0)
/LED94: D95.2 (K), U5.11 (OUT6)
/LED95: D96.2 (K), U5.12 (OUT7)
BLANK: R54.1, R56.2, R58.2, R59.2, R64.2, R67.1
BLANK1: R54.2, U8.29 (I2C2_SCL/USART3_TX/PB10)
BLANKCHANNEL: U8.17 (USART2_RX/ADC12_IN3/TIM2_CH4/PA3), U12.21 (OE)
CATHODE_1: U9.3 (Com-Cat), U9.8 (Com-Cat)
CATHODE_3: U11.3 (Com-Cat), U11.8 (Com-Cat)
DGND: C1.1, C3.1, C4.2, C7.2, C8.2, C9.2, C10.2, C11.2, C12.2, C13.1, C14.2, C15.1, C16.1, C17.2, C18.2, C19.2, C20.2, C21.2, C22.2, C23.2, C24.2, C25.2, C26.2, C30.1, C31.1, C32.1, C33.1, C34.1, C35.2, C36.2, C37.1, C38.2, C39.1, C40.2, C41.2, C42.2, C43.2, C44.2, C45.2, C46.2, C47.2, C48.2, C49.2, C50.2, C51.2, C52.2, C53.2, C54.2, C55.2, C56.1, C57.1, C58.1, C59.1, C61.2, JP1.1, P1.3, P1.4, P2.3, P2.4, P3.3, P3.5, P3.7, P3.9, P4.1, P4.3, P4.5, R1.1, R2.1, R3.1, R4.1, R5.1, R9.2, R19.2, R31.2, R73.1, S1.1 (G), S2.1 (G), S3.1 (G), S4.1 (G), S6.1 (G), S7.1 (G), S8.1 (G), U1.1 (GND), U3.1 (GND), U4.1 (GND), U5.1 (GND), U8.12 (VSSA), U8.18 (VSS), U8.28 (BOOT1/PB2), U8.31 (VSS), U8.47 (VSS), U8.60 (BOOT0), U8.63 (VSS), U12.1 (GND)
DISP1: U1.30 (XLAT), U8.30 (I2C2_SDA/USART3_RX/PB11)
DISP2: R35.2, U8.27 (ADC12_IN9/TIM3_CH4/PB1)
DISP3: R36.2, U8.26 (ADC12_IN8/TIM3_CH3/PB0)
DISP4: R52.2, U8.25 (PC5/ADC12_IN15)
DISP5: U8.20 (SPI1_NSS/USART2_CK/ADC12_IN4/PA4), U12.4 (LE)
I2CSCL: P4.2, U8.58 (I2C1_SCL/TIM4_CH1/PB6)
I2CSDA: P4.4, U8.59 (I2C1_SDA/TIM4_CH2/PB7)
NRST: C37.2, P3.10, U8.7 (~NRST)
unnamed: C18.1, R47.1, R53.1
unnamed: C28.1, U8.5 (PD0/OSC_IN), U13.1 (OSC)
unnamed: C29.2, R68.1, U13.3 (OSC)
unnamed: C36.1, R10.2
unnamed: L1.2, P1.5, P1.6
unnamed: L2.2, L3.2, P1.1, P1.2
unnamed: R1.2, U3.31 (IREF)
unnamed: R2.2, U4.31 (IREF)
unnamed: R3.2, U5.31 (IREF)
unnamed: R4.2, R55.1, S5.3, S5.4, S9.3, S9.4, S10.3, S10.4, S11.3, S11.4, S15.3, S15.4, S16.3, S16.4
unnamed: R7.2, U12.23 (REXT)
unnamed: R11.1, R40.2, S1.2 (A)
unnamed: R12.1, R41.2, S1.3 (B)
unnamed: R13.1, R42.2, S2.2 (A)
unnamed: R14.1, R43.2, S2.3 (B)
unnamed: R15.1, R48.2, S3.2 (A)
unnamed: R16.1, R49.2, S3.3 (B)
unnamed: R17.1, R50.2, S4.2 (A)
unnamed: R18.1, R51.2, S4.3 (B)
unnamed: R19.1, R20.2, S5.1, S5.2
unnamed: R20.1, R27.2, S9.1, S9.2
unnamed: R21.1, R46.2, S6.2 (A)
unnamed: R22.1, R47.2, S6.3 (B)
unnamed: R23.1, R38.2, S7.2 (A)
unnamed: R24.1, R39.2, S7.3 (B)
unnamed: R25.1, R44.2, S8.2 (A)
unnamed: R26.1, R45.2, S8.3 (B)
unnamed: R27.1, R28.2, S11.1, S11.2
unnamed: R28.1, R29.2, S10.1, S10.2
unnamed: R29.1, R30.2, S15.1, S15.2
unnamed: R31.1, R32.2, S14.1, S14.2
unnamed: R32.1, R33.2, S13.1, S13.2
unnamed: R35.1, R62.2
unnamed: R36.1, R63.2
unnamed: R52.1, R66.2
unnamed: R56.1, U1.2 (BLANK)
unnamed: R57.1, U1.4 (MOSI)
unnamed: R58.1, U3.2 (BLANK)
unnamed: R59.1, U4.2 (BLANK)
unnamed: R60.1, U3.4 (MOSI)
unnamed: R61.1, U4.4 (MOSI)
unnamed: R62.1, U3.30 (XLAT)
unnamed: R63.1, U4.30 (XLAT)
unnamed: R64.1, U5.2 (BLANK)
unnamed: R65.1, U5.4 (MOSI)
unnamed: R66.1, U5.30 (XLAT)
unnamed: R68.2, U8.6 (PD1/OSC_OUT)
unnamed: R73.2, U1.31 (IREF)
R1A: C7.1, R40.1, U8.33 (SPI2_NSS/I2C2_SMBA/USART3_CK/TIM1_BKIN/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)
R1B: C8.1, R41.1, U8.34 (SPI2_SCK/USART3_CTS/TIM1_CH1N/PB13)
R2A: C9.1, R42.1, U8.35 (SPI2_MISO/USART3_RTS/TIM1_CH2N/PB14)
R2B: C10.1, R43.1, U8.36 (SPI2_MOSI/TIM1_CH3N/PB15)
R3A: C19.1, R38.1, U8.37 (PC6)
R3B: C20.1, R39.1, U8.38 (PC7)
R4A: C21.1, R44.1, U8.39 (PC8)
R4B: C22.1, R45.1, U8.40 (PC9)
R5A: C11.1, R48.1, U8.41 (USART1_CK/TIM1_CH1/MCO/PA8)
R5B: C12.1, R49.1, U8.42 (USART1_TX/TIM1_CH2/PA9)
R6A: C13.2, R50.1, U8.43 (USART1_RX/TIM1_CH3/PA10)
R6B: C14.1, R51.1, U8.44 (USART1_CTS/CANRX/USBDM/TIM1_CH4/PA11)
R7A: C17.1, R46.1, U8.45 (USART1_RTS/CANTX/USBDP/TIM1_ETR/PA12)
R7B: R53.2, U8.62 (TIM4_CH4/PB9)
SEG_A: U9.7 (An-a), U10.7 (An-a), U11.7 (An-a)
SEG_B: U9.6 (An-b), U10.6 (An-b), U11.6 (An-b)
SEG_C: U9.4 (An-c), U10.4 (An-c), U11.4 (An-c)
SEG_D: U9.2 (An-d), U10.2 (An-d), U11.2 (An-d)
SEG_DP: U9.5 (An-dp), U10.5 (An-dp), U11.5 (An-dp)
SEG_E: U9.1 (An-e), U10.1 (An-e), U11.1 (An-e)
SEG_F: U9.9 (An-f), U10.9 (An-f), U11.9 (An-f)
SEG_G: U9.10 (An-g), U10.10 (An-g), U11.10 (An-g)
SPI1CLK: R8.2, R9.1, R10.1, U1.3 (CLK), U3.3 (CLK), U4.3 (CLK), U5.3 (CLK), U8.21 (SPI1_SCK/ADC12_IN5/PA5), U12.3 (CLK)
SPI1MOSI: U8.23 (SPI1_MOSI/ADC12_IN7/TIM3_CH2/PA7), U12.2 (SDI)
SPIMOSI: R57.2, R60.2, R61.2, R65.2
SWCLK: P3.4, U8.49 (JTCK/SWCLK/PA14)
SWDIO: P3.2, U8.46 (JTMS/SWDIO/PA13)
SWO: P3.6, U8.55 (JTDO/PB3)
SWRESET: P4.6, U8.61 (TIM4_CH3/PB8)
SWSPECIAL: R55.2, U8.16 (USART2_TX/ADC12_IN2/TIM2_CH3/PA2)
SWSTORE: R5.2, S12.3, S12.4, S13.3, S13.4, S14.3, S14.4, U8.15 (USART2_RTS/ADC12_IN1/TIM2_CH2/PA1)
xtalgnd: C28.2, C29.1, JP1.2, U13.2 (GND), U13.4 (GND)

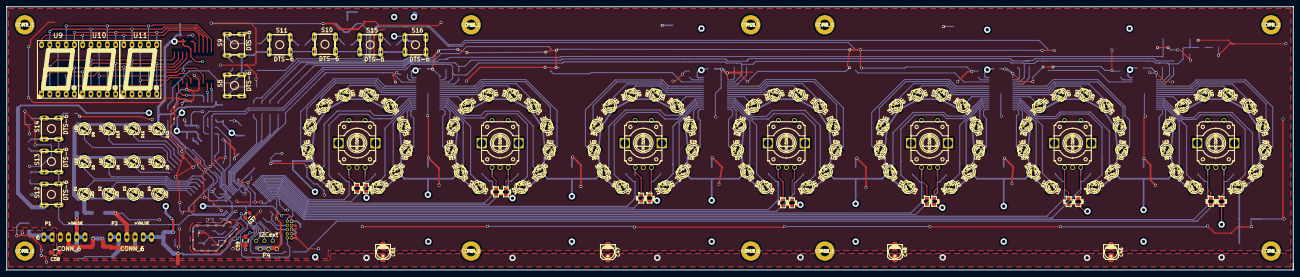
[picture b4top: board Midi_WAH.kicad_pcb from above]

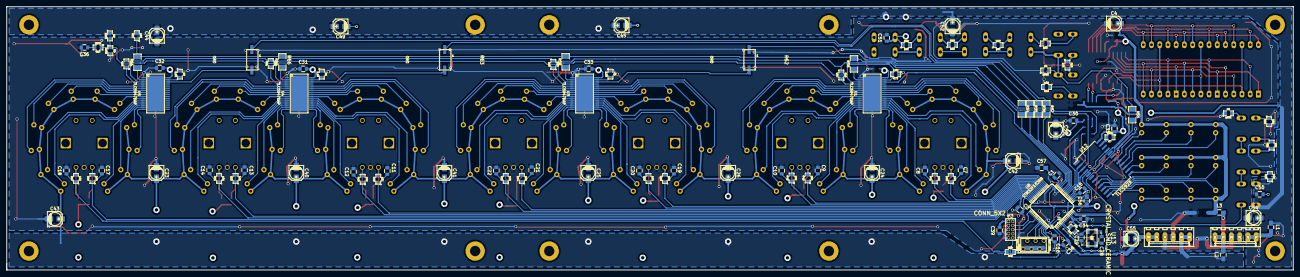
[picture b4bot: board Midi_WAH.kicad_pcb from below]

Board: 4 copper layers, 397.3 x 81.3 mm, 262 parts (116 on the bottom side), 192 nets.
